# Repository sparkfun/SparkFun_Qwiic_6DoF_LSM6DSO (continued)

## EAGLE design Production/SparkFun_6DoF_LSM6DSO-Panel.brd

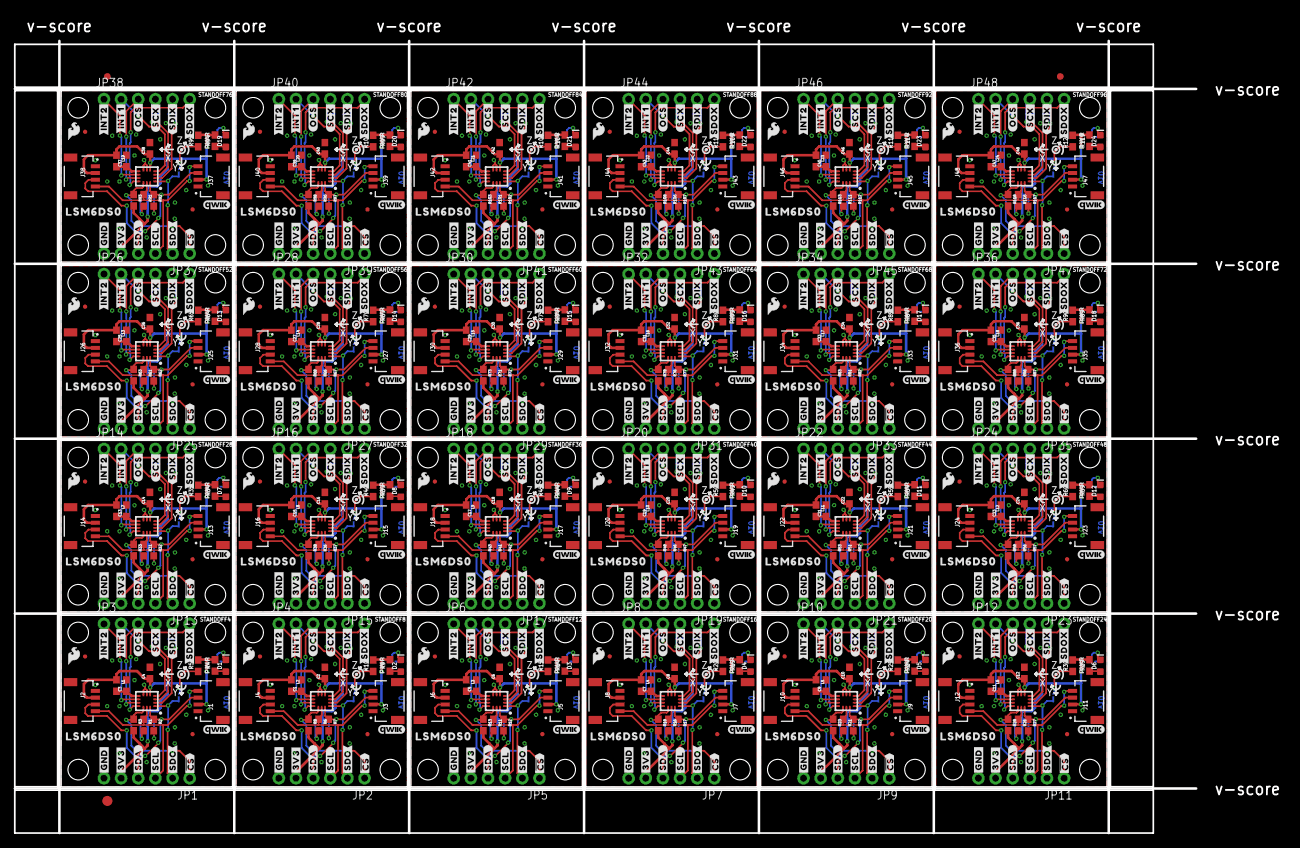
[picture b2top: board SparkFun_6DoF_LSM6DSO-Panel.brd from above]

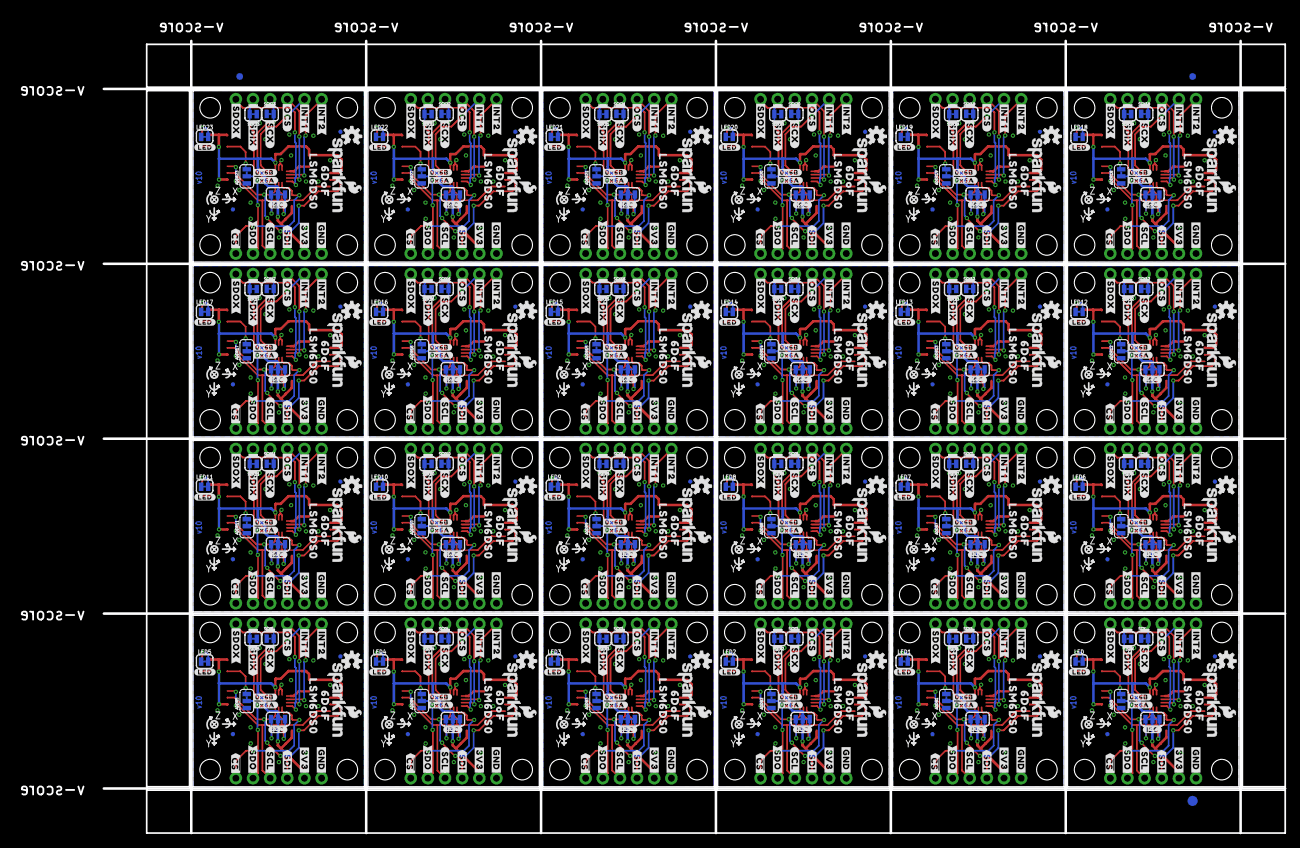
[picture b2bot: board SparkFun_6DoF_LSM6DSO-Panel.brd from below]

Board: 2 copper layers, 188.2 x 121.2 mm, 1518 parts (651 on the bottom side), 432 nets.

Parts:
ADDR, ADDR1, ADDR2, ADDR3, ADDR4, ADDR5, ADDR6, ADDR7, ADDR8, ADDR9, ADDR10, ADDR11, ADDR12, ADDR13, ADDR14, ADDR15, ADDR16, ADDR17, ADDR18, ADDR19, ADDR20, ADDR21, ADDR22, ADDR23: JUMPER-SMT_3_1-NC_TRACE_SILK; SMT-JUMPER_3_1-NC_TRACE_SILK
C1, C2, C3, C4, C5, C6, C7, C8, C9, C10, C11, C12, C13, C14, C15, C16, C17, C18, C19, C20, C21, C22, C23, C24, C25, C26, C27, C28, C29, C30, C31, C32, C33, C34, C35, C36, C37, C38, C39, C40, C41, C42, C43, C44, C45, C46, C47, C48: 0.1uF; 0603
D1, D2, D3, D4, D5, D6, D7, D8, D9, D10, D11, D12, D13, D14, D15, D16, D17, D18, D19, D20, D21, D22, D23, D24: LED-0603
E$1, E$2, E$3, E$4: FIDUCIAL-1X2
E$5, E$6: FIDUCIAL-1.5X3
FD1, FD2, FD3, FD4, FD5, FD6, FD7, FD8, FD9, FD10, FD11, FD12, FD13, FD14, FD15, FD16, FD17, FD18, FD19, FD20, FD21, FD22, FD23, FD24, FD25, FD26, FD27, FD28, FD29, FD30, FD31, FD32, FD33, FD34, FD35, FD36, FD37, FD38, FD39, FD40, FD41, FD42, FD43, FD44, FD45, FD46, FD47, FD48: FIDUCIALUFIDUCIAL; FIDUCIAL-MICRO
FID1, FID2, FID3, FID4, FID5, FID6, FID7, FID8, FID9, FID10, FID11, FID12, FID13, FID14, FID15, FID16, FID17, FID18, FID19, FID20, FID21, FID22, FID23, FID24, FID25, FID26, FID27, FID28, FID29, FID30, FID31, FID32, FID33, FID34, FID35, FID36, FID37, FID38, FID39, FID40, FID41, FID42, FID43, FID44, FID45, FID46, FID47, FID48: FIDUCIALUFIDUCIAL; FIDUCIAL-MICRO
I2C_PU, I2C_PU1, I2C_PU2, I2C_PU3, I2C_PU4, I2C_PU5, I2C_PU6, I2C_PU7, I2C_PU8, I2C_PU9, I2C_PU10, I2C_PU11, I2C_PU12, I2C_PU13, I2C_PU14, I2C_PU15, I2C_PU16, I2C_PU17, I2C_PU18, I2C_PU19, I2C_PU20, I2C_PU21, I2C_PU22, I2C_PU23: S_MODE; SMT-JUMPER_3_2-NC_TRACE_SILK
J1, J2, J3, J4, J5, J6, J7, J8, J9, J10, J11, J12, J13, J14, J15, J16, J17, J18, J19, J20, J21, J22, J23, J24, J25, J26, J27, J28, J29, J30, J31, J32, J33, J34, J35, J36, J37, J38, J39, J40, J41, J42, J43, J44, J45, J46, J47, J48: QWIIC_RIGHT_ANGLE; JST04_1MM_RA
JP1, JP2, JP3, JP4, JP5, JP6, JP7, JP8, JP9, JP10, JP11, JP12, JP13, JP14, JP15, JP16, JP17, JP18, JP19, JP20, JP21, JP22, JP23, JP24, JP25, JP26, JP27, JP28, JP29, JP30, JP31, JP32, JP33, JP34, JP35, JP36, JP37, JP38, JP39, JP40, JP41, JP42, JP43, JP44, JP45, JP46, JP47, JP48: IO; 1X06_NO_SILK
L1, L2, L3, L4, L5, L6, L7, L8, L9, L10, L11, L12, L13, L14, L15, L16, L17, L18, L19, L20, L21, L22, L23, L24: 30Ω; 0603
LED, LED1, LED2, LED3, LED4, LED5, LED6, LED7, LED8, LED9, LED10, LED11, LED12, LED13, LED14, LED15, LED16, LED17, LED18, LED19, LED20, LED21, LED22, LED23: JUMPER-SMT_2_NC_TRACE_SILK; SMT-JUMPER_2_NC_TRACE_SILK
LOGO1, LOGO6, LOGO9, LOGO12, LOGO15, LOGO18, LOGO21, LOGO24, LOGO27, LOGO30, LOGO33, LOGO36, LOGO39, LOGO42, LOGO45, LOGO48, LOGO51, LOGO54, LOGO57, LOGO60, LOGO63, LOGO66, LOGO69, LOGO72: QWIIC_LOGO_4MM; QWIIC_4MM
LOGO2, LOGO4, LOGO7, LOGO10, LOGO13, LOGO16, LOGO19, LOGO22, LOGO25, LOGO28, LOGO31, LOGO34, LOGO37, LOGO40, LOGO43, LOGO46, LOGO49, LOGO52, LOGO55, LOGO58, LOGO61, LOGO64, LOGO67, LOGO70: OSHW-LOGOS; OSHW-LOGO-S
LOGO3, LOGO5, LOGO8, LOGO11, LOGO14, LOGO17, LOGO20, LOGO23, LOGO26, LOGO29, LOGO32, LOGO35, LOGO38, LOGO41, LOGO44, LOGO47, LOGO50, LOGO53, LOGO56, LOGO59, LOGO62, LOGO65, LOGO68, LOGO71: SFE_LOGO_NAME_FLAME.1_INCH; SFE_LOGO_NAME_FLAME_.1
R1, R2, R6, R7, R11, R12, R16, R17, R21, R22, R26, R27, R31, R32, R36, R37, R41, R42, R46, R47, R51, R52, R56, R57, R61, R62, R66, R67, R71, R72, R76, R77, R81, R82, R86, R87, R91, R92, R96, R97, R101, R102, R106, R107, R111, R112, R116, R117: 4.7k; 0603
R3, R8, R13, R18, R23, R28, R33, R38, R43, R48, R53, R58, R63, R68, R73, R78, R83, R88, R93, R98, R103, R108, R113, R118: 10k; 0603
R4, R9, R14, R19, R24, R29, R34, R39, R44, R49, R54, R59, R64, R69, R74, R79, R84, R89, R94, R99, R104, R109, R114, R119: 1k; 0603
R5, R10, R15, R20, R25, R30, R35, R40, R45, R50, R55, R60, R65, R70, R75, R80, R85, R90, R95, R100, R105, R110, R115, R120: 100k; 0603
SCX, SCX1, SCX2, SCX3, SCX4, SCX5, SCX6, SCX7, SCX8, SCX9, SCX10, SCX11, SCX12, SCX13, SCX14, SCX15, SCX16, SCX17, SCX18, SCX19, SCX20, SCX21, SCX22, SCX23: JUMPER-SMT_2_NC_TRACE_SILK; SMT-JUMPER_2_NC_TRACE_SILK
SDX, SDX1, SDX2, SDX3, SDX4, SDX5, SDX6, SDX7, SDX8, SDX9, SDX10, SDX11, SDX12, SDX13, SDX14, SDX15, SDX16, SDX17, SDX18, SDX19, SDX20, SDX21, SDX22, SDX23: JUMPER-SMT_2_NC_TRACE_SILK; SMT-JUMPER_2_NC_TRACE_SILK
STANDOFF1, STANDOFF2, STANDOFF3, STANDOFF4, STANDOFF5, STANDOFF6, STANDOFF7, STANDOFF8, STANDOFF9, STANDOFF10, STANDOFF11, STANDOFF12, STANDOFF13, STANDOFF14, STANDOFF15, STANDOFF16, STANDOFF17, STANDOFF18, STANDOFF19, STANDOFF20, STANDOFF21, STANDOFF22, STANDOFF23, STANDOFF24, STANDOFF25, STANDOFF26, STANDOFF27, STANDOFF28, STANDOFF29, STANDOFF30, STANDOFF31, STANDOFF32, STANDOFF33, STANDOFF34, STANDOFF35, STANDOFF36, STANDOFF37, STANDOFF38, STANDOFF39, STANDOFF40, STANDOFF41, STANDOFF42, STANDOFF43, STANDOFF44, STANDOFF45, STANDOFF46, STANDOFF47, STANDOFF48, STANDOFF49, STANDOFF50, STANDOFF51, STANDOFF52, STANDOFF53, STANDOFF54, STANDOFF55, STANDOFF56, STANDOFF57, STANDOFF58, STANDOFF59, STANDOFF60, STANDOFF61, STANDOFF62, STANDOFF63, STANDOFF64, STANDOFF65, STANDOFF66, STANDOFF67, STANDOFF68, STANDOFF69, STANDOFF70, STANDOFF71, STANDOFF72, STANDOFF73, STANDOFF74, STANDOFF75, STANDOFF76, STANDOFF77, STANDOFF78, STANDOFF79, STANDOFF80, STANDOFF81, STANDOFF82, STANDOFF83, STANDOFF84, STANDOFF85, STANDOFF86, STANDOFF87, STANDOFF88, STANDOFF89, STANDOFF90, STANDOFF91, STANDOFF92, STANDOFF93, STANDOFF94, STANDOFF95, STANDOFF96: STAND-OFFTIGHT; STAND-OFF-TIGHT
U1, U2, U3, U4, U5, U6, U7, U8, U9, U10, U11, U12, U13, U14, U15, U16, U17, U18, U19, U20, U21, U22, U23, U24: LSM6DS0; LGA14L
U$1, U$15, U$34, U$41, U$67, U$74, U$100, U$107, U$133, U$140, U$166, U$173, U$199, U$206, U$232, U$239, U$265, U$272, U$298, U$305, U$331, U$338, U$364, U$371, U$397, U$404, U$430, U$437, U$463, U$470, U$496, U$503, U$529, U$536, U$562, U$569, U$595, U$602, U$628, U$635, U$661, U$668, U$694, U$701, U$727, U$734, U$760, U$767: #3V3#1
U$2, U$17, U$35, U$42, U$68, U$75, U$101, U$108, U$134, U$141, U$167, U$174, U$200, U$207, U$233, U$240, U$266, U$273, U$299, U$306, U$332, U$339, U$365, U$372, U$398, U$405, U$431, U$438, U$464, U$471, U$497, U$504, U$530, U$537, U$563, U$570, U$596, U$603, U$629, U$636, U$662, U$669, U$695, U$702, U$728, U$735, U$761, U$768: #GND#0
U$3, U$59, U$92, U$125, U$158, U$191, U$224, U$257, U$290, U$323, U$356, U$389, U$422, U$455, U$488, U$521, U$554, U$587, U$620, U$653, U$686, U$719, U$752, U$785: ##CS##7
U$4, U$36, U$69, U$102, U$135, U$168, U$201, U$234, U$267, U$300, U$333, U$366, U$399, U$432, U$465, U$498, U$531, U$564, U$597, U$630, U$663, U$696, U$729, U$762: #SDA#4
U$5, U$22, U$37, U$44, U$70, U$77, U$103, U$110, U$136, U$143, U$169, U$176, U$202, U$209, U$235, U$242, U$268, U$275, U$301, U$308, U$334, U$341, U$367, U$374, U$400, U$407, U$433, U$440, U$466, U$473, U$499, U$506, U$532, U$539, U$565, U$572, U$598, U$605, U$631, U$638, U$664, U$671, U$697, U$704, U$730, U$737, U$763, U$770: #SCL#5
U$6, U$53, U$86, U$119, U$152, U$185, U$218, U$251, U$284, U$317, U$350, U$383, U$416, U$449, U$482, U$515, U$548, U$581, U$614, U$647, U$680, U$713, U$746, U$779: #SDO#6
U$7, U$19, U$51, U$55, U$84, U$88, U$117, U$121, U$150, U$154, U$183, U$187, U$216, U$220, U$249, U$253, U$282, U$286, U$315, U$319, U$348, U$352, U$381, U$385, U$414, U$418, U$447, U$451, U$480, U$484, U$513, U$517, U$546, U$550, U$579, U$583, U$612, U$616, U$645, U$649, U$678, U$682, U$711, U$715, U$744, U$748, U$777, U$781: #INT1#9
U$8, U$21, U$52, U$56, U$85, U$89, U$118, U$122, U$151, U$155, U$184, U$188, U$217, U$221, U$250, U$254, U$283, U$287, U$316, U$320, U$349, U$353, U$382, U$386, U$415, U$419, U$448, U$452, U$481, U$485, U$514, U$518, U$547, U$551, U$580, U$584, U$613, U$617, U$646, U$650, U$679, U$683, U$712, U$716, U$745, U$749, U$778, U$782: #INT2#9
U$9, U$38, U$71, U$104, U$137, U$170, U$203, U$236, U$269, U$302, U$335, U$368, U$401, U$434, U$467, U$500, U$533, U$566, U$599, U$632, U$665, U$698, U$731, U$764: #OCS#8
U$10, U$39, U$72, U$105, U$138, U$171, U$204, U$237, U$270, U$303, U$336, U$369, U$402, U$435, U$468, U$501, U$534, U$567, U$600, U$633, U$666, U$699, U$732, U$765: #SCX#9
U$11, U$33, U$63, U$66, U$96, U$99, U$129, U$132, U$162, U$165, U$195, U$198, U$228, U$231, U$261, U$264, U$294, U$297, U$327, U$330, U$360, U$363, U$393, U$396, U$426, U$429, U$459, U$462, U$492, U$495, U$525, U$528, U$558, U$561, U$591, U$594, U$624, U$627, U$657, U$660, U$690, U$693, U$723, U$726, U$756, U$759, U$789, U$792: #SDIX#11
U$12, U$30, U$40, U$58, U$73, U$91, U$106, U$124, U$139, U$157, U$172, U$190, U$205, U$223, U$238, U$256, U$271, U$289, U$304, U$322, U$337, U$355, U$370, U$388, U$403, U$421, U$436, U$454, U$469, U$487, U$502, U$520, U$535, U$553, U$568, U$586, U$601, U$619, U$634, U$652, U$667, U$685, U$700, U$718, U$733, U$751, U$766, U$784: LSM6DS011
U$13, U$47, U$80, U$113, U$146, U$179, U$212, U$245, U$278, U$311, U$344, U$377, U$410, U$443, U$476, U$509, U$542, U$575, U$608, U$641, U$674, U$707, U$740, U$773: #0X6A#11
U$14, U$48, U$81, U$114, U$147, U$180, U$213, U$246, U$279, U$312, U$345, U$378, U$411, U$444, U$477, U$510, U$543, U$576, U$609, U$642, U$675, U$708, U$741, U$774: #0X6B#11
U$16, U$46, U$79, U$112, U$145, U$178, U$211, U$244, U$277, U$310, U$343, U$376, U$409, U$442, U$475, U$508, U$541, U$574, U$607, U$640, U$673, U$706, U$739, U$772: #LED#11
U$18, U$54, U$87, U$120, U$153, U$186, U$219, U$252, U$285, U$318, U$351, U$384, U$417, U$450, U$483, U$516, U$549, U$582, U$615, U$648, U$681, U$714, U$747, U$780: #SDO#7
U$20, U$43, U$76, U$109, U$142, U$175, U$208, U$241, U$274, U$307, U$340, U$373, U$406, U$439, U$472, U$505, U$538, U$571, U$604, U$637, U$670, U$703, U$736, U$769: #OCS#7
U$23, U$45, U$78, U$111, U$144, U$177, U$210, U$243, U$276, U$309, U$342, U$375, U$408, U$441, U$474, U$507, U$540, U$573, U$606, U$639, U$672, U$705, U$738, U$771: #SCX#8
U$24, U$32, U$64, U$65, U$97, U$98, U$130, U$131, U$163, U$164, U$196, U$197, U$229, U$230, U$262, U$263, U$295, U$296, U$328, U$329, U$361, U$362, U$394, U$395, U$427, U$428, U$460, U$461, U$493, U$494, U$526, U$527, U$559, U$560, U$592, U$593, U$625, U$626, U$658, U$659, U$691, U$692, U$724, U$725, U$757, U$758, U$790, U$791: #SDOX#12
U$25, U$49, U$82, U$115, U$148, U$181, U$214, U$247, U$280, U$313, U$346, U$379, U$412, U$445, U$478, U$511, U$544, U$577, U$610, U$643, U$676, U$709, U$742, U$775: #I2C#11
U$26, U$57, U$90, U$123, U$156, U$189, U$222, U$255, U$288, U$321, U$354, U$387, U$420, U$453, U$486, U$519, U$552, U$585, U$618, U$651, U$684, U$717, U$750, U$783: #SDI#4
U$27, U$60, U$93, U$126, U$159, U$192, U$225, U$258, U$291, U$324, U$357, U$390, U$423, U$456, U$489, U$522, U$555, U$588, U$621, U$654, U$687, U$720, U$753, U$786: ##CS##8
U$28, U$50, U$83, U$116, U$149, U$182, U$215, U$248, U$281, U$314, U$347, U$380, U$413, U$446, U$479, U$512, U$545, U$578, U$611, U$644, U$677, U$710, U$743, U$776: PWR8
U$29, U$62, U$95, U$128, U$161, U$194, U$227, U$260, U$293, U$326, U$359, U$392, U$425, U$458, U$491, U$524, U$557, U$590, U$623, U$656, U$689, U$722, U$755, U$788: SFE_LOGO_FLAME_.1
U$31, U$61, U$94, U$127, U$160, U$193, U$226, U$259, U$292, U$325, U$358, U$391, U$424, U$457, U$490, U$523, U$556, U$589, U$622, U$655, U$688, U$721, U$754, U$787: 6DOF12

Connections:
3.3V: C4.1, I2C_PU.2, J1.2, J2.2, JP1.5, L1.1, R3.2, R4.2, R5.2, U1.5
3.3V1: C2.1, I2C_PU1.2, J3.2, J4.2, JP2.5, L2.1, R8.2, R9.2, R10.2, U2.5
3.3V2: C6.1, I2C_PU2.2, J5.2, J6.2, JP5.5, L3.1, R13.2, R14.2, R15.2, U3.5
3.3V3: C8.1, I2C_PU3.2, J7.2, J8.2, JP7.5, L4.1, R18.2, R19.2, R20.2, U4.5
3.3V4: C10.1, I2C_PU4.2, J9.2, J10.2, JP9.5, L5.1, R23.2, R24.2, R25.2, U5.5
3.3V5: C12.1, I2C_PU5.2, J11.2, J12.2, JP11.5, L6.1, R28.2, R29.2, R30.2, U6.5
3.3V6: C14.1, I2C_PU6.2, J13.2, J14.2, JP13.5, L7.1, R33.2, R34.2, R35.2, U7.5
3.3V7: C16.1, I2C_PU7.2, J15.2, J16.2, JP15.5, L8.1, R38.2, R39.2, R40.2, U8.5
3.3V8: C18.1, I2C_PU8.2, J17.2, J18.2, JP17.5, L9.1, R43.2, R44.2, R45.2, U9.5
3.3V9: C20.1, I2C_PU9.2, J19.2, J20.2, JP19.5, L10.1, R48.2, R49.2, R50.2, U10.5
3.3V10: C22.1, I2C_PU10.2, J21.2, J22.2, JP21.5, L11.1, R53.2, R54.2, R55.2, U11.5
3.3V11: C24.1, I2C_PU11.2, J23.2, J24.2, JP23.5, L12.1, R58.2, R59.2, R60.2, U12.5
3.3V12: C26.1, I2C_PU12.2, J25.2, J26.2, JP25.5, L13.1, R63.2, R64.2, R65.2, U13.5
3.3V13: C28.1, I2C_PU13.2, J27.2, J28.2, JP27.5, L14.1, R68.2, R69.2, R70.2, U14.5
3.3V14: C30.1, I2C_PU14.2, J29.2, J30.2, JP29.5, L15.1, R73.2, R74.2, R75.2, U15.5
3.3V15: C32.1, I2C_PU15.2, J31.2, J32.2, JP31.5, L16.1, R78.2, R79.2, R80.2, U16.5
3.3V16: C34.1, I2C_PU16.2, J33.2, J34.2, JP33.5, L17.1, R83.2, R84.2, R85.2, U17.5
3.3V17: C36.1, I2C_PU17.2, J35.2, J36.2, JP35.5, L18.1, R88.2, R89.2, R90.2, U18.5
3.3V18: C38.1, I2C_PU18.2, J37.2, J38.2, JP37.5, L19.1, R93.2, R94.2, R95.2, U19.5
3.3V19: C40.1, I2C_PU19.2, J39.2, J40.2, JP39.5, L20.1, R98.2, R99.2, R100.2, U20.5
3.3V20: C42.1, I2C_PU20.2, J41.2, J42.2, JP41.5, L21.1, R103.2, R104.2, R105.2, U21.5
3.3V21: C44.1, I2C_PU21.2, J43.2, J44.2, JP43.5, L22.1, R108.2, R109.2, R110.2, U22.5
3.3V22: C46.1, I2C_PU22.2, J45.2, J46.2, JP45.5, L23.1, R113.2, R114.2, R115.2, U23.5
3.3V23: C48.1, I2C_PU23.2, J47.2, J48.2, JP47.5, L24.1, R118.2, R119.2, R120.2, U24.5
!CS!: JP1.1, R3.1, U1.12
!CS!1: JP2.1, R8.1, U2.12
!CS!2: JP5.1, R13.1, U3.12
!CS!3: JP7.1, R18.1, U4.12
!CS!4: JP9.1, R23.1, U5.12
!CS!5: JP11.1, R28.1, U6.12
!CS!6: JP13.1, R33.1, U7.12
!CS!7: JP15.1, R38.1, U8.12
!CS!8: JP17.1, R43.1, U9.12
!CS!9: JP19.1, R48.1, U10.12
!CS!10: JP21.1, R53.1, U11.12
!CS!11: JP23.1, R58.1, U12.12
!CS!12: JP25.1, R63.1, U13.12
!CS!13: JP27.1, R68.1, U14.12
!CS!14: JP29.1, R73.1, U15.12
!CS!15: JP31.1, R78.1, U16.12
!CS!16: JP33.1, R83.1, U17.12
!CS!17: JP35.1, R88.1, U18.12
!CS!18: JP37.1, R93.1, U19.12
!CS!19: JP39.1, R98.1, U20.12
!CS!20: JP41.1, R103.1, U21.12
!CS!21: JP43.1, R108.1, U22.12
!CS!22: JP45.1, R113.1, U23.12
!CS!23: JP47.1, R118.1, U24.12
GND: ADDR.1, C3.2, C4.2, J1.1, J2.1, JP1.6, LED.1, SCX.1, SDX.1, U1.6, U1.7
GND1: ADDR1.1, C1.2, C2.2, J3.1, J4.1, JP2.6, LED1.1, SCX1.1, SDX1.1, U2.6, U2.7
GND2: ADDR2.1, C5.2, C6.2, J5.1, J6.1, JP5.6, LED2.1, SCX2.1, SDX2.1, U3.6, U3.7
GND3: ADDR3.1, C7.2, C8.2, J7.1, J8.1, JP7.6, LED3.1, SCX3.1, SDX3.1, U4.6, U4.7
GND4: ADDR4.1, C9.2, C10.2, J9.1, J10.1, JP9.6, LED4.1, SCX4.1, SDX4.1, U5.6, U5.7
GND5: ADDR5.1, C11.2, C12.2, J11.1, J12.1, JP11.6, LED5.1, SCX5.1, SDX5.1, U6.6, U6.7
GND6: ADDR6.1, C13.2, C14.2, J13.1, J14.1, JP13.6, LED6.1, SCX6.1, SDX6.1, U7.6, U7.7
GND7: ADDR7.1, C15.2, C16.2, J15.1, J16.1, JP15.6, LED7.1, SCX7.1, SDX7.1, U8.6, U8.7
GND8: ADDR8.1, C17.2, C18.2, J17.1, J18.1, JP17.6, LED8.1, SCX8.1, SDX8.1, U9.6, U9.7
GND9: ADDR9.1, C19.2, C20.2, J19.1, J20.1, JP19.6, LED9.1, SCX9.1, SDX9.1, U10.6, U10.7
GND10: ADDR10.1, C21.2, C22.2, J21.1, J22.1, JP21.6, LED10.1, SCX10.1, SDX10.1, U11.6, U11.7
GND11: ADDR11.1, C23.2, C24.2, J23.1, J24.1, JP23.6, LED11.1, SCX11.1, SDX11.1, U12.6, U12.7
GND12: ADDR12.1, C25.2, C26.2, J25.1, J26.1, JP25.6, LED12.1, SCX12.1, SDX12.1, U13.6, U13.7
GND13: ADDR13.1, C27.2, C28.2, J27.1, J28.1, JP27.6, LED13.1, SCX13.1, SDX13.1, U14.6, U14.7
GND14: ADDR14.1, C29.2, C30.2, J29.1, J30.1, JP29.6, LED14.1, SCX14.1, SDX14.1, U15.6, U15.7
GND15: ADDR15.1, C31.2, C32.2, J31.1, J32.1, JP31.6, LED15.1, SCX15.1, SDX15.1, U16.6, U16.7
GND16: ADDR16.1, C33.2, C34.2, J33.1, J34.1, JP33.6, LED16.1, SCX16.1, SDX16.1, U17.6, U17.7
GND17: ADDR17.1, C35.2, C36.2, J35.1, J36.1, JP35.6, LED17.1, SCX17.1, SDX17.1, U18.6, U18.7
GND18: ADDR18.1, C37.2, C38.2, J37.1, J38.1, JP37.6, LED18.1, SCX18.1, SDX18.1, U19.6, U19.7
GND19: ADDR19.1, C39.2, C40.2, J39.1, J40.1, JP39.6, LED19.1, SCX19.1, SDX19.1, U20.6, U20.7
GND20: ADDR20.1, C41.2, C42.2, J41.1, J42.1, JP41.6, LED20.1, SCX20.1, SDX20.1, U21.6, U21.7
GND21: ADDR21.1, C43.2, C44.2, J43.1, J44.1, JP43.6, LED21.1, SCX21.1, SDX21.1, U22.6, U22.7
GND22: ADDR22.1, C45.2, C46.2, J45.1, J46.1, JP45.6, LED22.1, SCX22.1, SDX22.1, U23.6, U23.7
GND23: ADDR23.1, C47.2, C48.2, J47.1, J48.1, JP47.6, LED23.1, SCX23.1, SDX23.1, U24.6, U24.7
INT1: JP3.2, U1.4
INT2: JP3.1, U1.9
INT3: JP4.2, U2.4
INT4: JP4.1, U2.9
INT5: JP6.2, U3.4
INT6: JP6.1, U3.9
INT7: JP8.2, U4.4
INT8: JP8.1, U4.9
INT9: JP10.2, U5.4
INT10: JP10.1, U5.9
INT11: JP12.2, U6.4
INT12: JP12.1, U6.9
INT13: JP14.2, U7.4
INT14: JP14.1, U7.9
INT15: JP16.2, U8.4
INT16: JP16.1, U8.9
INT17: JP18.2, U9.4
INT18: JP18.1, U9.9
INT19: JP20.2, U10.4
INT20: JP20.1, U10.9
INT21: JP22.2, U11.4
INT22: JP22.1, U11.9
INT23: JP24.2, U12.4
INT24: JP24.1, U12.9
INT25: JP26.2, U13.4
INT26: JP26.1, U13.9
INT27: JP28.2, U14.4
INT28: JP28.1, U14.9
INT29: JP30.2, U15.4
INT30: JP30.1, U15.9
INT31: JP32.2, U16.4
INT32: JP32.1, U16.9
INT33: JP34.2, U17.4
INT34: JP34.1, U17.9
INT35: JP36.2, U18.4
INT36: JP36.1, U18.9
INT37: JP38.2, U19.4
INT38: JP38.1, U19.9
INT39: JP40.2, U20.4
INT40: JP40.1, U20.9
INT41: JP42.2, U21.4
INT42: JP42.1, U21.9
INT43: JP44.2, U22.4
INT44: JP44.1, U22.9
INT45: JP46.2, U23.4
INT46: JP46.1, U23.9
INT47: JP48.2, U24.4
INT48: JP48.1, U24.9
unnamed: ADDR.3, R5.1
unnamed: D1.A, R4.1
unnamed: D1.C, LED.2
unnamed: I2C_PU1.1, R6.2
unnamed: I2C_PU.1, R1.2
unnamed: I2C_PU.3, R2.2
unnamed: I2C_PU1.3, R7.2
unnamed: D2.A, R9.1
unnamed: D2.C, LED1.2
unnamed: ADDR1.3, R10.1
unnamed: I2C_PU2.1, R11.2
unnamed: I2C_PU2.3, R12.2
unnamed: D3.A, R14.1
unnamed: D3.C, LED2.2
unnamed: ADDR2.3, R15.1
unnamed: I2C_PU3.1, R16.2
unnamed: I2C_PU3.3, R17.2
unnamed: D4.A, R19.1
unnamed: D4.C, LED3.2
unnamed: ADDR3.3, R20.1
unnamed: I2C_PU4.1, R21.2
unnamed: I2C_PU4.3, R22.2
unnamed: D5.A, R24.1
unnamed: D5.C, LED4.2
unnamed: ADDR4.3, R25.1
unnamed: I2C_PU5.1, R26.2
unnamed: I2C_PU5.3, R27.2
unnamed: D6.A, R29.1
unnamed: D6.C, LED5.2
unnamed: ADDR5.3, R30.1
unnamed: I2C_PU6.1, R31.2
unnamed: I2C_PU6.3, R32.2
unnamed: D7.A, R34.1
unnamed: D7.C, LED6.2
unnamed: ADDR6.3, R35.1
unnamed: I2C_PU7.1, R36.2
unnamed: I2C_PU7.3, R37.2
unnamed: D8.A, R39.1
unnamed: D8.C, LED7.2
unnamed: ADDR7.3, R40.1
unnamed: I2C_PU8.1, R41.2
unnamed: I2C_PU8.3, R42.2
unnamed: D9.A, R44.1
unnamed: D9.C, LED8.2
unnamed: ADDR8.3, R45.1
unnamed: I2C_PU9.1, R46.2
unnamed: I2C_PU9.3, R47.2
unnamed: D10.A, R49.1
unnamed: D10.C, LED9.2
unnamed: ADDR9.3, R50.1
unnamed: I2C_PU10.1, R51.2
unnamed: I2C_PU10.3, R52.2
unnamed: D11.A, R54.1
unnamed: D11.C, LED10.2
unnamed: ADDR10.3, R55.1
unnamed: I2C_PU11.1, R56.2
unnamed: I2C_PU11.3, R57.2
unnamed: D12.A, R59.1
unnamed: D12.C, LED11.2
unnamed: ADDR11.3, R60.1
unnamed: I2C_PU12.1, R61.2
unnamed: I2C_PU12.3, R62.2
unnamed: D13.A, R64.1
unnamed: D13.C, LED12.2
unnamed: ADDR12.3, R65.1
unnamed: I2C_PU13.1, R66.2
unnamed: I2C_PU13.3, R67.2
unnamed: D14.A, R69.1
unnamed: D14.C, LED13.2
unnamed: ADDR13.3, R70.1
unnamed: I2C_PU14.1, R71.2
unnamed: I2C_PU14.3, R72.2
unnamed: D15.A, R74.1
unnamed: D15.C, LED14.2
unnamed: ADDR14.3, R75.1
unnamed: I2C_PU15.1, R76.2
unnamed: I2C_PU15.3, R77.2
unnamed: D16.A, R79.1
unnamed: D16.C, LED15.2
unnamed: ADDR15.3, R80.1
unnamed: I2C_PU16.1, R81.2
unnamed: I2C_PU16.3, R82.2
unnamed: D17.A, R84.1
unnamed: D17.C, LED16.2
unnamed: ADDR16.3, R85.1
unnamed: I2C_PU17.1, R86.2
unnamed: I2C_PU17.3, R87.2
unnamed: D18.A, R89.1
unnamed: D18.C, LED17.2
unnamed: ADDR17.3, R90.1
unnamed: I2C_PU18.1, R91.2
unnamed: I2C_PU18.3, R92.2
unnamed: D19.A, R94.1
unnamed: D19.C, LED18.2
unnamed: ADDR18.3, R95.1
unnamed: I2C_PU19.1, R96.2
unnamed: I2C_PU19.3, R97.2
unnamed: D20.A, R99.1
unnamed: D20.C, LED19.2
unnamed: ADDR19.3, R100.1
unnamed: I2C_PU20.1, R101.2
unnamed: I2C_PU20.3, R102.2
unnamed: D21.A, R104.1
unnamed: D21.C, LED20.2
unnamed: ADDR20.3, R105.1
unnamed: I2C_PU21.1, R106.2
unnamed: I2C_PU21.3, R107.2
unnamed: D22.A, R109.1
unnamed: D22.C, LED21.2
unnamed: ADDR21.3, R110.1
unnamed: I2C_PU22.1, R111.2
unnamed: I2C_PU22.3, R112.2
unnamed: D23.A, R114.1
unnamed: D23.C, LED22.2
unnamed: ADDR22.3, R115.1
unnamed: I2C_PU23.1, R116.2
unnamed: I2C_PU23.3, R117.2
unnamed: D24.A, R119.1
unnamed: D24.C, LED23.2
unnamed: ADDR23.3, R120.1
OCS: JP3.3, U1.10
OCS1: JP4.3, U2.10
OCS2: JP6.3, U3.10
OCS3: JP8.3, U4.10
OCS4: JP10.3, U5.10
OCS5: JP12.3, U6.10
OCS6: JP14.3, U7.10
OCS7: JP16.3, U8.10
OCS8: JP18.3, U9.10
OCS9: JP20.3, U10.10
OCS10: JP22.3, U11.10
OCS11: JP24.3, U12.10
OCS12: JP26.3, U13.10
OCS13: JP28.3, U14.10
OCS14: JP30.3, U15.10
OCS15: JP32.3, U16.10
OCS16: JP34.3, U17.10
OCS17: JP36.3, U18.10
OCS18: JP38.3, U19.10
OCS19: JP40.3, U20.10
OCS20: JP42.3, U21.10
OCS21: JP44.3, U22.10
OCS22: JP46.3, U23.10
OCS23: JP48.3, U24.10
SCL: J1.4, J2.4, JP1.3, R1.1, U1.13
SCL1: J3.4, J4.4, JP2.3, R6.1, U2.13
SCL2: J5.4, J6.4, JP5.3, R11.1, U3.13
SCL3: J7.4, J8.4, JP7.3, R16.1, U4.13
SCL4: J9.4, J10.4, JP9.3, R21.1, U5.13
SCL5: J11.4, J12.4, JP11.3, R26.1, U6.13
SCL6: J13.4, J14.4, JP13.3, R31.1, U7.13
SCL7: J15.4, J16.4, JP15.3, R36.1, U8.13
SCL8: J17.4, J18.4, JP17.3, R41.1, U9.13
SCL9: J19.4, J20.4, JP19.3, R46.1, U10.13
SCL10: J21.4, J22.4, JP21.3, R51.1, U11.13
SCL11: J23.4, J24.4, JP23.3, R56.1, U12.13
SCL12: J25.4, J26.4, JP25.3, R61.1, U13.13
SCL13: J27.4, J28.4, JP27.3, R66.1, U14.13
SCL14: J29.4, J30.4, JP29.3, R71.1, U15.13
SCL15: J31.4, J32.4, JP31.3, R76.1, U16.13
SCL16: J33.4, J34.4, JP33.3, R81.1, U17.13
SCL17: J35.4, J36.4, JP35.3, R86.1, U18.13
SCL18: J37.4, J38.4, JP37.3, R91.1, U19.13
SCL19: J39.4, J40.4, JP39.3, R96.1, U20.13
SCL20: J41.4, J42.4, JP41.3, R101.1, U21.13
SCL21: J43.4, J44.4, JP43.3, R106.1, U22.13
SCL22: J45.4, J46.4, JP45.3, R111.1, U23.13
SCL23: J47.4, J48.4, JP47.3, R116.1, U24.13
SCX: JP3.4, SCX.2, U1.3
SCX1: JP4.4, SCX1.2, U2.3
SCX2: JP6.4, SCX2.2, U3.3
SCX3: JP8.4, SCX3.2, U4.3
SCX4: JP10.4, SCX4.2, U5.3
SCX5: JP12.4, SCX5.2, U6.3
SCX6: JP14.4, SCX6.2, U7.3
SCX7: JP16.4, SCX7.2, U8.3
SCX8: JP18.4, SCX8.2, U9.3
SCX9: JP20.4, SCX9.2, U10.3
SCX10: JP22.4, SCX10.2, U11.3
SCX11: JP24.4, SCX11.2, U12.3
SCX12: JP26.4, SCX12.2, U13.3
SCX13: JP28.4, SCX13.2, U14.3
SCX14: JP30.4, SCX14.2, U15.3
SCX15: JP32.4, SCX15.2, U16.3
SCX16: JP34.4, SCX16.2, U17.3
SCX17: JP36.4, SCX17.2, U18.3
SCX18: JP38.4, SCX18.2, U19.3
SCX19: JP40.4, SCX19.2, U20.3
SCX20: JP42.4, SCX20.2, U21.3
SCX21: JP44.4, SCX21.2, U22.3
SCX22: JP46.4, SCX22.2, U23.3
SCX23: JP48.4, SCX23.2, U24.3
SDA: J1.3, J2.3, JP1.4, R2.1, U1.14
SDA1: J3.3, J4.3, JP2.4, R7.1, U2.14
SDA2: J5.3, J6.3, JP5.4, R12.1, U3.14
SDA3: J7.3, J8.3, JP7.4, R17.1, U4.14
SDA4: J9.3, J10.3, JP9.4, R22.1, U5.14
SDA5: J11.3, J12.3, JP11.4, R27.1, U6.14
SDA6: J13.3, J14.3, JP13.4, R32.1, U7.14
SDA7: J15.3, J16.3, JP15.4, R37.1, U8.14
SDA8: J17.3, J18.3, JP17.4, R42.1, U9.14
SDA9: J19.3, J20.3, JP19.4, R47.1, U10.14
SDA10: J21.3, J22.3, JP21.4, R52.1, U11.14
SDA11: J23.3, J24.3, JP23.4, R57.1, U12.14
SDA12: J25.3, J26.3, JP25.4, R62.1, U13.14
SDA13: J27.3, J28.3, JP27.4, R67.1, U14.14
SDA14: J29.3, J30.3, JP29.4, R72.1, U15.14
SDA15: J31.3, J32.3, JP31.4, R77.1, U16.14
SDA16: J33.3, J34.3, JP33.4, R82.1, U17.14
SDA17: J35.3, J36.3, JP35.4, R87.1, U18.14
SDA18: J37.3, J38.3, JP37.4, R92.1, U19.14
SDA19: J39.3, J40.3, JP39.4, R97.1, U20.14
SDA20: J41.3, J42.3, JP41.4, R102.1, U21.14
SDA21: J43.3, J44.3, JP43.4, R107.1, U22.14
SDA22: J45.3, J46.3, JP45.4, R112.1, U23.14
SDA23: J47.3, J48.3, JP47.4, R117.1, U24.14
SDI_AUX: JP3.5, SDX.2, U1.2
SDI_AUX1: JP4.5, SDX1.2, U2.2
SDI_AUX2: JP6.5, SDX2.2, U3.2
SDI_AUX3: JP8.5, SDX3.2, U4.2
SDI_AUX4: JP10.5, SDX4.2, U5.2
SDI_AUX5: JP12.5, SDX5.2, U6.2
SDI_AUX6: JP14.5, SDX6.2, U7.2
SDI_AUX7: JP16.5, SDX7.2, U8.2
SDI_AUX8: JP18.5, SDX8.2, U9.2
SDI_AUX9: JP20.5, SDX9.2, U10.2
SDI_AUX10: JP22.5, SDX10.2, U11.2
SDI_AUX11: JP24.5, SDX11.2, U12.2
SDI_AUX12: JP26.5, SDX12.2, U13.2
SDI_AUX13: JP28.5, SDX13.2, U14.2
SDI_AUX14: JP30.5, SDX14.2, U15.2
SDI_AUX15: JP32.5, SDX15.2, U16.2
SDI_AUX16: JP34.5, SDX16.2, U17.2
SDI_AUX17: JP36.5, SDX17.2, U18.2
SDI_AUX18: JP38.5, SDX18.2, U19.2
SDI_AUX19: JP40.5, SDX19.2, U20.2
SDI_AUX20: JP42.5, SDX20.2, U21.2
SDI_AUX21: JP44.5, SDX21.2, U22.2
SDI_AUX22: JP46.5, SDX22.2, U23.2
SDI_AUX23: JP48.5, SDX23.2, U24.2
SDO/SA0: ADDR.2, JP1.2, U1.1
SDO/SA1: ADDR1.2, JP2.2, U2.1
SDO/SA2: ADDR2.2, JP5.2, U3.1
SDO/SA3: ADDR3.2, JP7.2, U4.1
SDO/SA4: ADDR4.2, JP9.2, U5.1
SDO/SA5: ADDR5.2, JP11.2, U6.1
SDO/SA6: ADDR6.2, JP13.2, U7.1
SDO/SA7: ADDR7.2, JP15.2, U8.1
SDO/SA8: ADDR8.2, JP17.2, U9.1
SDO/SA9: ADDR9.2, JP19.2, U10.1
SDO/SA10: ADDR10.2, JP21.2, U11.1
SDO/SA11: ADDR11.2, JP23.2, U12.1
SDO/SA12: ADDR12.2, JP25.2, U13.1
SDO/SA13: ADDR13.2, JP27.2, U14.1
SDO/SA14: ADDR14.2, JP29.2, U15.1
SDO/SA15: ADDR15.2, JP31.2, U16.1
SDO/SA16: ADDR16.2, JP33.2, U17.1
SDO/SA17: ADDR17.2, JP35.2, U18.1
SDO/SA18: ADDR18.2, JP37.2, U19.1
SDO/SA19: ADDR19.2, JP39.2, U20.1
SDO/SA20: ADDR20.2, JP41.2, U21.1
SDO/SA21: ADDR21.2, JP43.2, U22.1
SDO/SA22: ADDR22.2, JP45.2, U23.1
SDO/SA23: ADDR23.2, JP47.2, U24.1
SDO_AUX: JP3.6, U1.11
SDO_AUX1: JP4.6, U2.11
SDO_AUX2: JP6.6, U3.11
SDO_AUX3: JP8.6, U4.11
SDO_AUX4: JP10.6, U5.11
SDO_AUX5: JP12.6, U6.11
SDO_AUX6: JP14.6, U7.11
SDO_AUX7: JP16.6, U8.11
SDO_AUX8: JP18.6, U9.11
SDO_AUX9: JP20.6, U10.11
SDO_AUX10: JP22.6, U11.11
SDO_AUX11: JP24.6, U12.11
SDO_AUX12: JP26.6, U13.11
SDO_AUX13: JP28.6, U14.11
SDO_AUX14: JP30.6, U15.11
SDO_AUX15: JP32.6, U16.11
SDO_AUX16: JP34.6, U17.11
SDO_AUX17: JP36.6, U18.11
SDO_AUX18: JP38.6, U19.11
SDO_AUX19: JP40.6, U20.11
SDO_AUX20: JP42.6, U21.11
SDO_AUX21: JP44.6, U22.11
SDO_AUX22: JP46.6, U23.11
SDO_AUX23: JP48.6, U24.11
VDD: C3.1, L1.2, U1.8
VDD1: C1.1, L2.2, U2.8
VDD2: C5.1, L3.2, U3.8
VDD3: C7.1, L4.2, U4.8
VDD4: C9.1, L5.2, U5.8
VDD5: C11.1, L6.2, U6.8
VDD6: C13.1, L7.2, U7.8
VDD7: C15.1, L8.2, U8.8
VDD8: C17.1, L9.2, U9.8
VDD9: C19.1, L10.2, U10.8
VDD10: C21.1, L11.2, U11.8
VDD11: C23.1, L12.2, U12.8
VDD12: C25.1, L13.2, U13.8
VDD13: C27.1, L14.2, U14.8
VDD14: C29.1, L15.2, U15.8
VDD15: C31.1, L16.2, U16.8
VDD16: C33.1, L17.2, U17.8
VDD17: C35.1, L18.2, U18.8
VDD18: C37.1, L19.2, U19.8
VDD19: C39.1, L20.2, U20.8
VDD20: C41.1, L21.2, U21.8
VDD21: C43.1, L22.2, U22.8
VDD22: C45.1, L23.2, U23.8
VDD23: C47.1, L24.2, U24.8

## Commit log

2021-02-23 Fixes input/output labels of respective silk, adds better text description to jumpers
2021-02-23 Adds VDD and VDDIO voltage range to schematic
    * Moves some traces and vias that were too close to the standoffs
    * Adds SparkFun flame and name of product to topside
2021-02-25 Updates LSM6D0 with axes, fixes measures, removes references to "slave/master" terminology
    * Removes inner standoffs
    * Centers IC
    * Adds 100k pullup to SDO/SA0 net
2021-02-25 Fixes silk overlap
2021-02-25 Updates IC with production ID, adjusts connector section
2021-02-25 Adds SDO_AUX to header, updates symbol to have more consistent labeling
    * Approves some minor DRC errors
2021-02-26 Fixes silk on SDOX and SDIX to be OUTPUT/INPUT respectively
2021-02-26 Moves a trace for better ground pour, adds production panel
2021-04-22 Adds red LED with PROD_ID to schematic
2022-02-28 Removes temp library and uses LSM6DSO IC from SparkFun Eagle Libraries.
